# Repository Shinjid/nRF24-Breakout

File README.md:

# nRF24-Breakout
Kicad nRF24 breakout board project. Designed while taking the Udemy course "Tech Explorations: Kicad Like a Pro"

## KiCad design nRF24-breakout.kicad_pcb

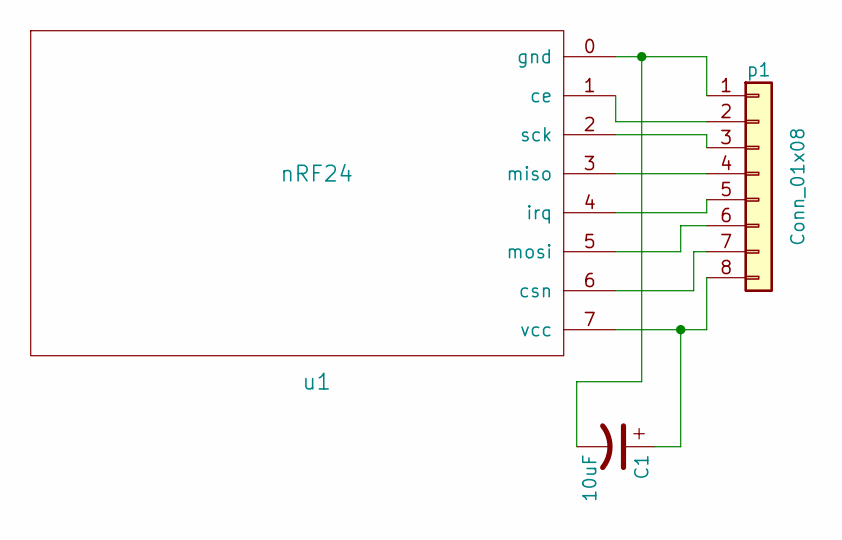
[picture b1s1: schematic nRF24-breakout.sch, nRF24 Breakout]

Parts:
C1: 10uF; CP_Radial_D10.0mm_P5.00mm
p1: Conn_01x08; Pin_Header_Straight_1x08_Pitch2.54mm
u1: nRF24

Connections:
unnamed: C1.1, p1.8, u1.7 (vcc)
unnamed: C1.2, p1.1, u1.0 (gnd)
unnamed: p1.2, u1.1 (ce)
unnamed: p1.3, u1.2 (sck)
unnamed: p1.4, u1.3 (miso)
unnamed: p1.5, u1.4 (irq)
unnamed: p1.6, u1.5 (mosi)
unnamed: p1.7, u1.6 (csn)

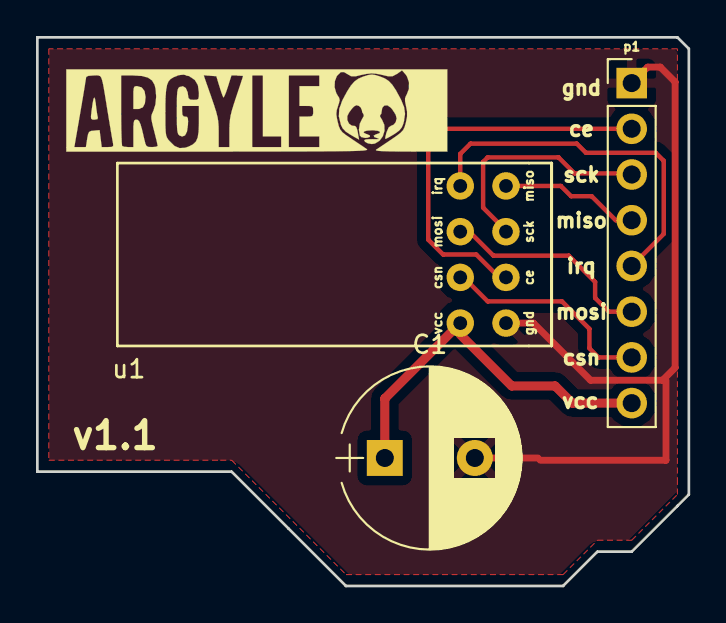
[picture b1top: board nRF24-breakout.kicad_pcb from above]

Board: 2 copper layers, 36.2 x 30.5 mm, 3 parts (0 on the bottom side), 8 nets.

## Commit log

2018-06-28 initial commit for nRF24-breakout
2018-06-28 readme
2018-06-28 adding gerber files
